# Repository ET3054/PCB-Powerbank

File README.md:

# PCB-Powerbank

Ziel ist eine Powerbank mit ca. 12000mAh Kapazität.
Es soll eine Schutzschaltung geben.
Eine Ladeanzeige soll ebenfalls verbaut sein.

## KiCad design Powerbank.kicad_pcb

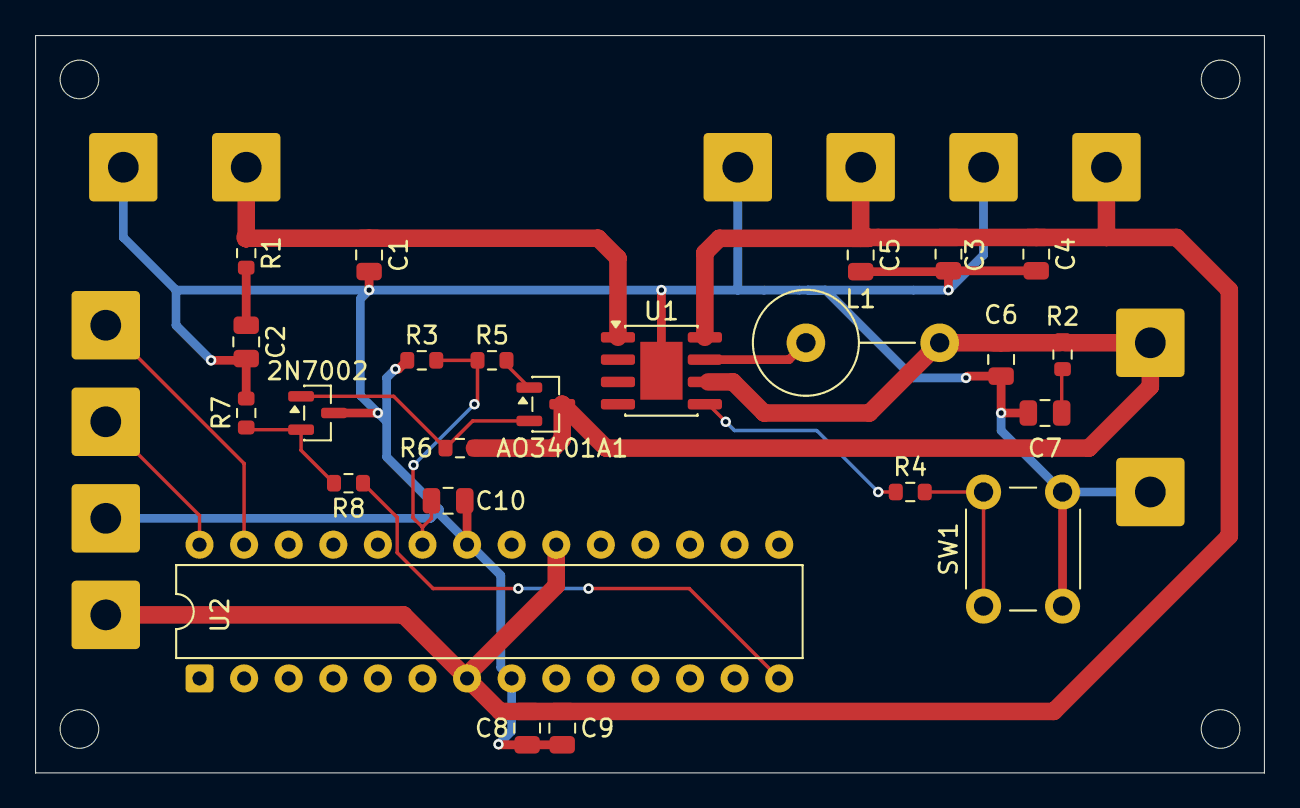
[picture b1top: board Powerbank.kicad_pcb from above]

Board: 2 copper layers, 70.0 x 42.0 mm, 24 parts (0 on the bottom side), 14 nets.

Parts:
2N7002: NMOS; SOT-23
AO3401A1: PMOS; SOT-23
C1, C2, C6, C7: 10µF; C_0805_2012Metric
C3, C4, C5: 22µF; C_0805_2012Metric
C8, C9, C10: 100nF; C_0805_2012Metric
L1: 1µH; L_Axial_L14.5mm_D5.8mm_P7.62mm_Vertical_Fastron_HBCC
R1, R2: 2Ω; R_0603_1608Metric
R3, R8: 10kΩ; R_0603_1608Metric
R4: 10000Ω; R_0603_1608Metric
R5: 33kΩ; R_0603_1608Metric
R6, R7: 100kΩ; R_0603_1608Metric
SW1: SW_Push; SW_PUSH_6mm
U1: IP5306; SOIC-8-1EP_3.9x4.9mm_P1.27mm_EP2.41x3.3mm
U2: ATmega328-P; DIP-28_W7.62mm

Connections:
+BATT: AO3401A1.3 (S), C6.1, L1.2, R2.1, R6.1, U1.6 (BAT)
GND: 2N7002.3 (S), C1.2, C2.2, C3.2, C4.2, C5.2, C6.2, C7.2, C8.2, C9.2, C10.2, R3.1, R7.2, SW1.2, U1.9 (EP), U2.8 (GND), U2.22 (GND)
unnamed: 2N7002.1 (D), AO3401A1.2 (G), R6.2
unnamed: 2N7002.2 (G), R7.1, R8.2
unnamed: AO3401A1.1 (D), R5.2
unnamed: C2.1, R1.2
unnamed: C7.1, R2.2
unnamed: C3.1, C4.1, C5.1, C8.1, C9.1, U1.8 (VOUT), U2.7 (VCC), U2.20 (AVCC)
unnamed: C1.1, R1.1, U1.1 (VIN)
unnamed: R4.2, SW1.1
unnamed: R4.1, U1.5 (KEY)
unnamed: L1.1, U1.7 (SW)
unnamed: R8.1, U2.14 (PB0)
unnamed: C10.1, R3.2, R5.1, U2.23 (PC0)
